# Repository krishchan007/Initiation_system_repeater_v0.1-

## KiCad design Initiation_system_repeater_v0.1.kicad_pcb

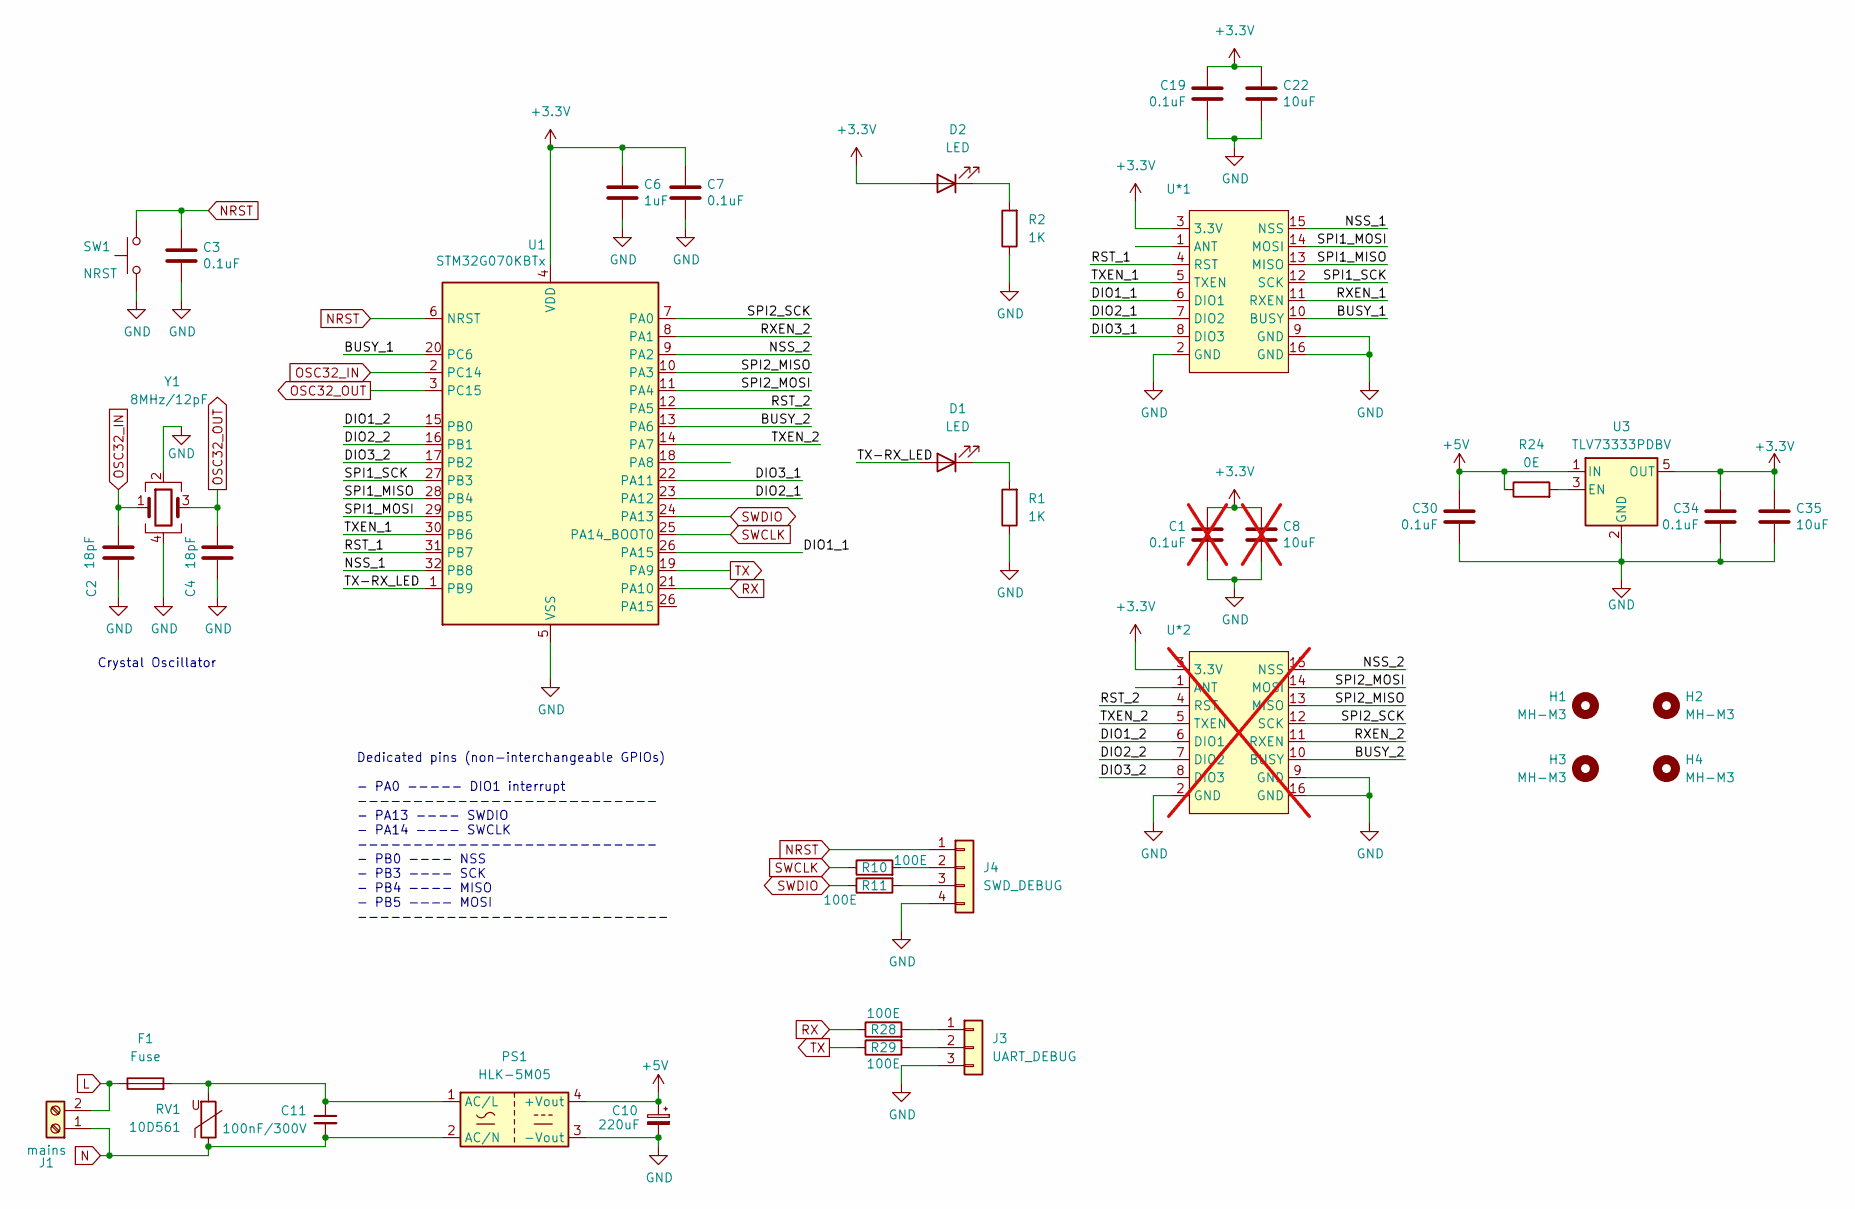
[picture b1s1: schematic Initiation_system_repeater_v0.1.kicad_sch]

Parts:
C1: 0.1uF; C_0603_1608Metric; not fitted
C2, C4: 18pF; C_0603_1608Metric_Pad1.08x0.95mm_HandSolder
C3, C7, C19, C30, C34: 0.1uF; C_0603_1608Metric
C6: 1uF; C_0603_1608Metric
C8: 10uF; C_0603_1608Metric; not fitted
C10: 220uF; CP_Elec_6.3x5.4
C11: 100nF/300V; C_Rect_L16.5mm_W4.9mm_P15.00mm_MKT
C22, C35: 10uF; C_0603_1608Metric
D1, D2: LED; LED_0603_1608Metric_Pad1.05x0.95mm_HandSolder
F1: Fuse; Fuseholder_Clip-5x20mm_Littelfuse_111_Inline_P20.00x5.00mm_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
H1, H2, H3, H4: MH-M3; MountingHole_2.2mm_M2_ISO7380
J1: mains; TerminalBlock_bornier-2_P5.08mm
J3: UART_DEBUG; PinHeader_1x03_P2.54mm_Horizontal
J4: SWD_DEBUG; PinHeader_1x04_P2.54mm_Horizontal
PS1: HLK-5M05; Converter_ACDC_Hi-Link_HLK-5Mxx
R1, R2: 1K; R_0603_1608Metric
R10, R11, R28, R29: 100E; R_0603_1608Metric
R24: 0E; R_0603_1608Metric
RV1: 10D561; MOV10D561KTR
SW1: NRST; SW_DIP_SPSTx01_Slide_6.7x4.1mm_W6.73mm_P2.54mm_LowProfile_J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
U1: STM32G070KBTx; LQFP-32_7x7mm_P0.8mm
U3: TLV73333PDBV; SOT-23-5
U*1: ISC-SX1262-B
U*2: ISC-SX1262-B; not fitted
Y1: 8MHz/12pF; Crystal_SMD_3225-4Pin_3.2x2.5mm

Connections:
+3.3V: C1.1, C6.1, C7.1, C8.1, C19.1, C22.1, C34.1, C35.1, D2.2 (A), U1.4 (VDD), U3.5 (OUT), U*1.3 (3.3V), U*2.3 (3.3V)
+5V: C10.1, C30.1, PS1.4 (+Vout), R24.1, U3.1 (IN)
/BUSY_1: U1.20 (PC6), U*1.10 (BUSY)
/BUSY_2: U1.13 (PA6), U*2.10 (BUSY)
/DIO1_1: U1.26 (PA15), U*1.6 (DIO1)
/DIO1_2: U1.15 (PB0), U*2.6 (DIO1)
/DIO2_1: U1.23 (PA12), U*1.7 (DIO2)
/DIO2_2: U1.16 (PB1), U*2.7 (DIO2)
/DIO3_1: U1.22 (PA11), U*1.8 (DIO3)
/DIO3_2: U1.17 (PB2), U*2.8 (DIO3)
/NSS_1: U1.32 (PB8), U*1.15 (NSS)
/NSS_2: U1.9 (PA2), U*2.15 (NSS)
/RST_1: U1.31 (PB7), U*1.4 (RST)
/RST_2: U1.12 (PA5), U*2.4 (RST)
/RXEN_1: U*1.11 (RXEN)
/RXEN_2: U1.8 (PA1), U*2.11 (RXEN)
/SPI1_MISO: U1.28 (PB4), U*1.13 (MISO)
/SPI1_MOSI: U1.29 (PB5), U*1.14 (MOSI)
/SPI1_SCK: U1.27 (PB3), U*1.12 (SCK)
/SPI2_MISO: U1.10 (PA3), U*2.13 (MISO)
/SPI2_MOSI: U1.11 (PA4), U*2.14 (MOSI)
/SPI2_SCK: U1.7 (PA0), U*2.12 (SCK)
/TX-RX_LED: D1.2 (A), U1.1 (PB9)
/TXEN_1: U1.30 (PB6), U*1.5 (TXEN)
/TXEN_2: U1.14 (PA7), U*2.5 (TXEN)
GND: C1.2, C2.2, C3.1, C4.2, C6.2, C7.2, C8.2, C10.2, C19.2, C22.2, C30.2, C34.2, C35.2, J3.3, J4.4, PS1.3 (-Vout), R1.1, R2.1, SW1.1, U1.5 (VSS), U3.2 (GND), U*1.2 (GND), U*1.9 (GND), U*1.16 (GND), U*2.2 (GND), U*2.9 (GND), U*2.16 (GND), Y1.2, Y1.4
L: F1.1, J1.2
N: C11.2, J1.1, PS1.2 (AC/N), RV1.1
NRST: C3.2, J4.1, SW1.2, U1.6 (NRST)
unnamed: D1.1 (K), R1.2
unnamed: D2.1 (K), R2.2
unnamed: J3.1, R28.2
unnamed: J3.2, R29.2
unnamed: J4.2, R10.2
unnamed: J4.3, R11.2
unnamed: C11.1, F1.2, PS1.1 (AC/L), RV1.2
unnamed: R24.2, U3.3 (EN)
OSC32_IN: C2.1, U1.2 (PC14), Y1.1
OSC32_OUT: C4.1, U1.3 (PC15), Y1.3
RX: R28.1, U1.21 (PA10)
SWCLK: R10.1, U1.25 (PA14_BOOT0)
SWDIO: R11.1, U1.24 (PA13)
TX: R29.1, U1.19 (PA9)

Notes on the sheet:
Crystal Oscillator
Dedicated pins (non-interchangeable GPIOs) - PA0 ----- DIO1 interrupt --------------------------- - PA13 ---- SWDIO - PA14 ---- SWCLK --------------------------- - PB0 ---- NSS - PB3 ---- SCK - PB4 ---- MISO - PB5 ---- MOSI ----------------------------

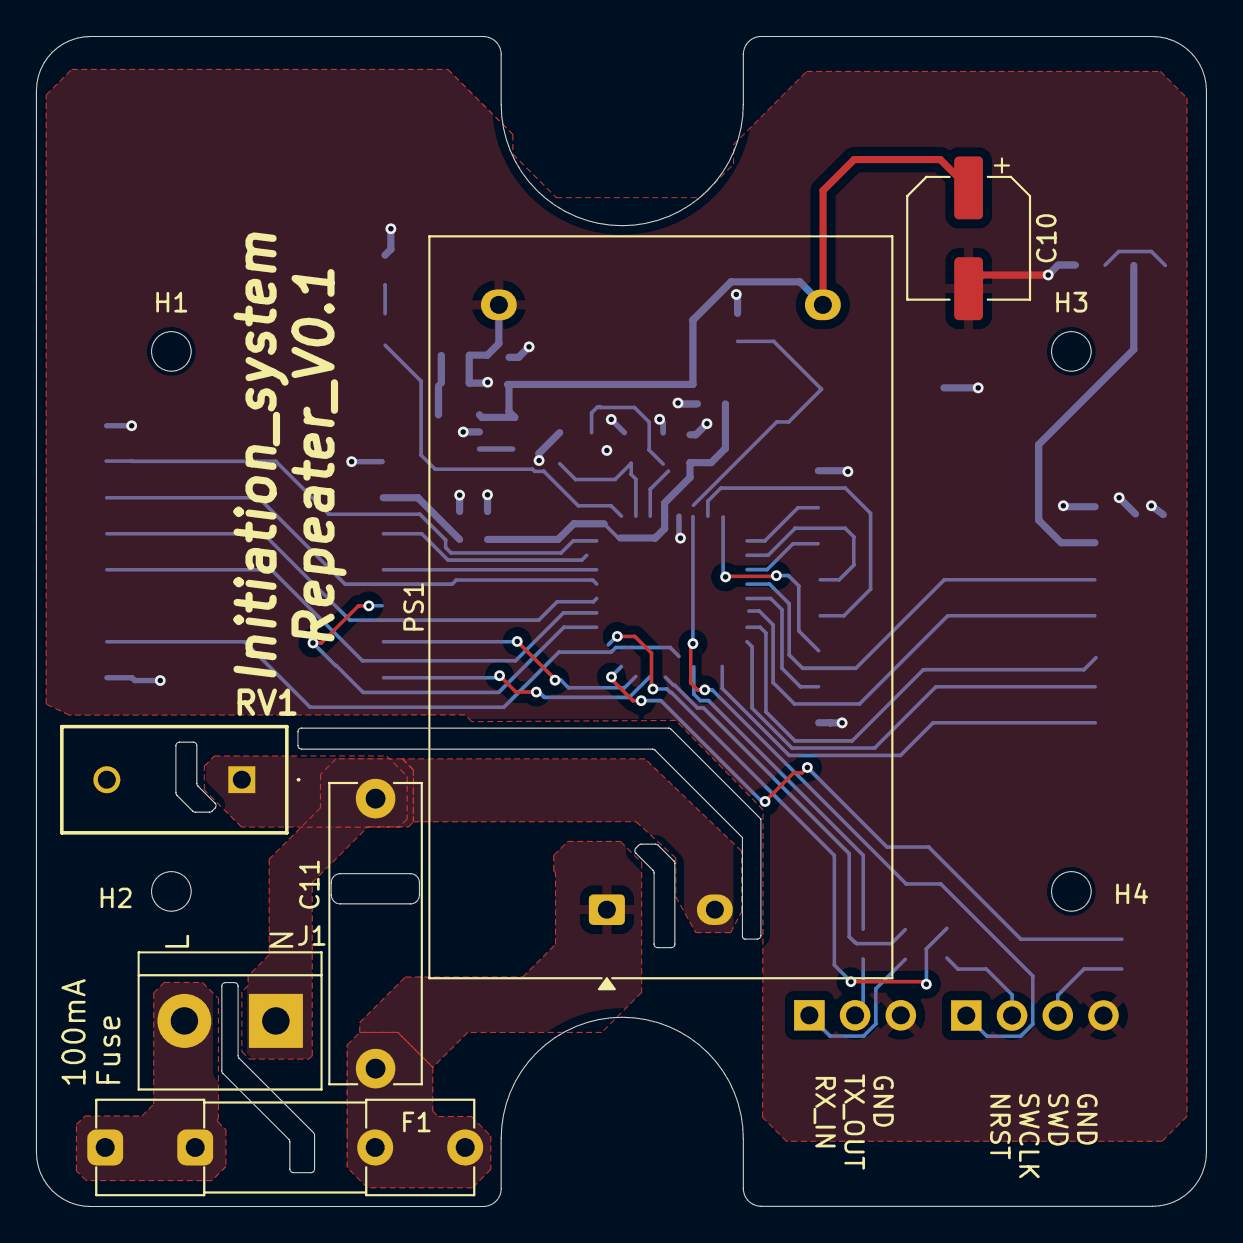
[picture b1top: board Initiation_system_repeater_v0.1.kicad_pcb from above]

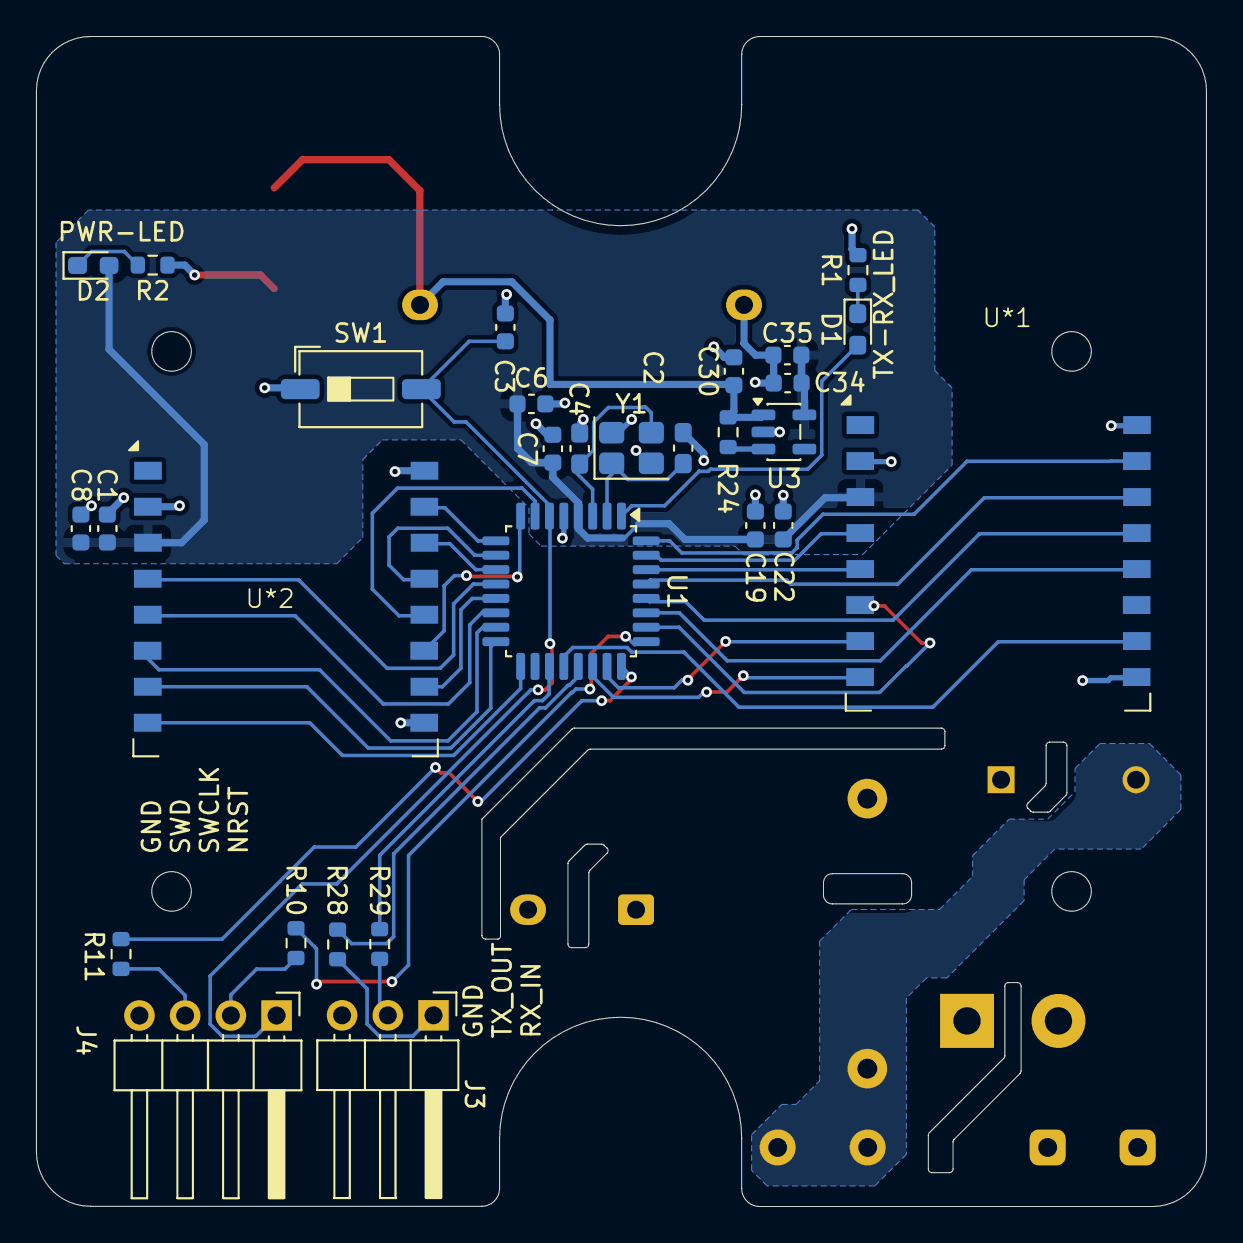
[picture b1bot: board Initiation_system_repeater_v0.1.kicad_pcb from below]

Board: 2 copper layers, 65.0 x 65.0 mm, 39 parts (29 on the bottom side), 42 nets.

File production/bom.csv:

Designator,Footprint,Quantity,Value,LCSC Part #
"C1, C19, C3, C30, C34, C7",0603,6,0.1uF,
C10,CP_Elec_6.3x5.4,1,220uF,
C11,C_Rect_L16.5mm_W4.9mm_P15.00mm_MKT,1,100nF/300V,
"C2, C4",0603,2,18pF,
"C22, C35, C8",0603,3,10uF,
C6,0603,1,1uF,
"D1, D2",0603,2,LED,
F1,Fuseholder_Clip-5x20mm_Littelfuse_111_Inline_P20.00x5.00mm_D1.05mm_Horizontal,1,Fuse,
J1,TerminalBlock_bornier-2_P5.08mm,1,mains,
J3,PinHeader_1x03_P2.54mm_Horizontal,1,UART_DEBUG,
J4,PinHeader_1x04_P2.54mm_Horizontal,1,SWD_DEBUG,
PS1,Converter_ACDC_Hi-Link_HLK-5Mxx,1,HLK-5M05,
"R1, R2",0603,2,1K,
"R10, R11, R28, R29",0603,4,100E,
R24,0603,1,0E,
RV1,MOV10D561KTR,1,10D561,
SW1,SW_DIP_SPSTx01_Slide_6.7x4.1mm_W6.73mm_P2.54mm_LowProfile_JPin,1,NRST,
"U*1, U*2",ISC-SX1262-B,2,~,
U1,LQFP-32_7x7mm_P0.8mm,1,STM32G070KBTx,
U3,SOT-23-5,1,TLV73333PDBV,
Y1,Crystal_SMD_3225-4Pin_3.2x2.5mm,1,8MHz/12pF,
